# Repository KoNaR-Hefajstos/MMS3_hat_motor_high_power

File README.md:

# Hat Motor High Power

Dostosowany do 48V, ale można zmienić XXX żeby pracować na większym napięciu aż do 100V

Up to 100V 10A

# Dokumentacja
https://github.com/Themuse061/Moducard_System_Handbook

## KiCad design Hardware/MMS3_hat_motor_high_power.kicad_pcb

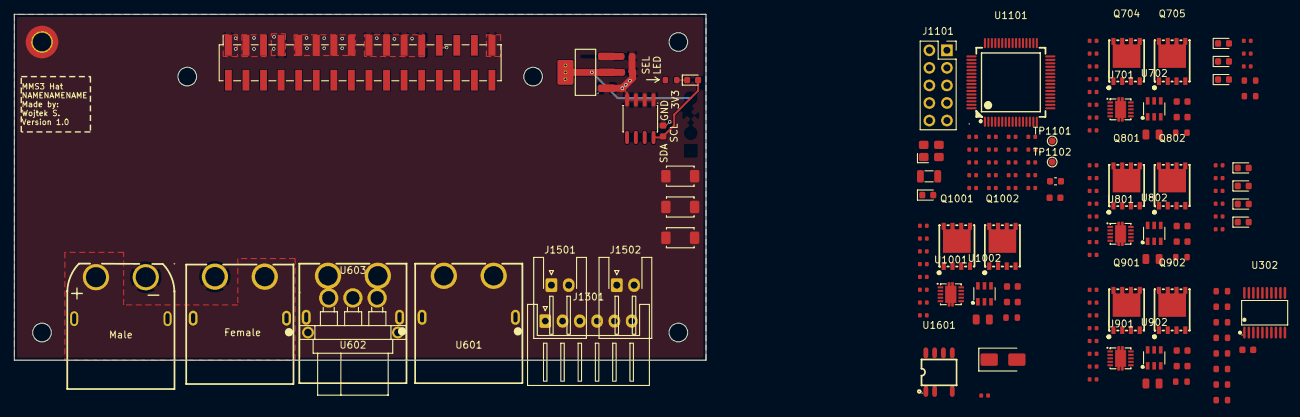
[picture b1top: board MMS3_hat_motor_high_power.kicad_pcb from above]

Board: 2 copper layers, 100.0 x 50.0 mm, 150 parts (1 on the bottom side), 117 nets.

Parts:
C101, C102, C1101: 10uF; C_0603
C301, C501, C703, C704, C802, C804, C902, C904, C1002, C1004: 100nF; C_0603
C701, C708, C803, C808, C903, C908, C1003, C1008, C1102, C1105, C1107, C1109, C1110, C1113, C1114: 100nF; C_0402
C702, C801, C901, C1001: 4.7uF; C_0805
C1103, C1111: 22pF; C_0402
C1104, C1108: 12pF; C_0402
C1106, C1112: 10uF; C_0402
CN401: XT60PW-M; C98732_CONN-TH_XT60PW-M
D301, D601, D603, D607, D1501, D1502, D1503, D1504: Red; D_0603
D401: M7; D_SMA
D701, D801, D901, D1001: D_TVS; R_0402
D1101: Yellow; D_0603
FB1101: FB_0603
H101: M2.5 Mount; MountingHole_2.7mm_M2.5_DIN965_Pad_TopOnly
H102, H103, H104, H105, H106: M2.5 mount; MountingHole_2.7mm_M2.5
J201: Chainbus in; PinHeader_2x16_P2.54mm_Vertical_SMD
J202: Chainbus Out; PinSocket_2x16_P2.54mm_Vertical_SMD
J1101: WCH Link; PinSocket_2x05_P2.54mm_Vertical
J1301: Conn_01x06; JST_XH_S6B-XH-A_1x06_P2.50mm_Horizontal
J1501, J1502: Conn_01x02; JST_XH_S2B-XH-A-1_1x02_P2.50mm_Horizontal
Q704, Q705, Q801, Q802, Q901, Q902, Q1001, Q1002: XRS80N12F; C42457090_DFN-8_L5_8-W4_9-P1_27-LS6_1-BL
R301, R302, R303, R304, R307, R308, R309, R312: 10kΩ; R_0603
R311: 1kΩ; R_0603
R601, R604, R703, R802, R902, R1002: 220kΩ; R_0603
R602, R704, R804, R904, R1004: 6.8kΩ; R_0402
R603, R1107, R1501, R1502, R1503, R1504: 1kΩ; R_0402
R605: 12kΩ; R_0402
R701, R702, R801, R803, R901, R903, R1001, R1003, R1101: 0Ω; R_0402
R706, R707, R806, R807, R906, R907, R1006, R1007, R1102, R1103, R1104, R1105, R1106, R1401, R1505, R1506: 10kΩ; R_0402
S1101, S1102, S1103: Tactile Button, 160gf; SW_TS-1088-AR02016
TP1101, TP1102: TestPoint; TestPoint_Pad_D1.0mm
U101: AMS1117; SOT-223-3_L6.5-W3.4-P2.30-LS7.0-BR
U302: SN74CB3Q3245PWR; C470961_TSSOP-20_L6_5-W4_4-P0_65-LS6_4-BL
U401, U601, U602: XT60PW-F_C428722; C428722_TH_2P-XT60PW-F
U501: M24C64; SOIC-8_L5.0-W4.0-P1.27-LS6.0-BL
U603: MR30PW-F20.G.Y; C19268035_CONN-TH_MR30PW-F
U701, U801, U901, U1001: UCC27302ADRCR; C50092311_VSON-10_L3_0-W3_0-P0_50-TL-EP
U702, U802, U902, U1002: INA181A2IDBVR(LX); C53198613_SOT-23-6_L2_9-W1_6-P0_95-LS2_8-BL
U1101: CH32V305RBT6; C5187529_LQFP-64_L10_0-W10_0-P0_50-LS12_0-BL
U1601: LNK3204D-TL; C567600_SO-8C_7P-L4_9-W3_9-P1_27-LS6_0-BL-PE3
X1101: X322525MOB4SI; OSC-SMD_4P-L3.2-W2.5-BL
X1102: Q13FC1350000400; FC-135R_L3.2-W1.5

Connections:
+3V3: C102.1, C301.1, C501.1, C708.1, C808.1, C908.1, C1008.1, C1101.1, C1102.1, C1105.1, C1106.1, C1107.1, C1110.1, D301.2, FB1101.1, J1101.8, J1301.2, J1501.1, J1502.1, R301.1, R302.1, R304.1, R308.1, R312.1, R603.1, R707.1, R807.1, R907.1, R1007.1, R1101.1, R1104.1, R1105.1, R1401.1, S1101.1 (A), S1102.1 (A), TP1101.1 (1_1), U101.2 (VOUT), U101.4 (VOUT), U302.20 (VCC), U501.8 (VCC), U702.6 (VS), U802.6 (VS), U902.6 (VS), U1002.6 (VS), U1101.19 (VDD_4), U1101.32 (VIO_1), U1101.48 (VDD_2), U1101.64 (VIO_3)
+5V: C101.1, J201.3, J201.5, J202.3, J202.5, J1101.10, U101.3 (VIN)
+12V: C702.1, C703.1, C801.1, C802.1, C901.1, C902.1, C1001.1, C1002.1, R605.1, U701.1 (VDD), U801.1 (VDD), U901.1 (VDD), U1001.1 (VDD)
+12V stby: J201.29, J202.29
/Bus_switch/Chainbus.SCL: R304.2, U302.11 (B8), U501.6 (SCL)
/Bus_switch/Chainbus.SDA: R308.2, U302.12 (B7), U501.5 (SDA)
/Bus_switch/Chainbus_In.CS: J201.22, J202.22, U302.7 (A6)
/Bus_switch/Chainbus_In.MISO: J201.28, J202.28, U302.4 (A3)
/Bus_switch/Chainbus_In.MOSI: J201.26, J202.26, U302.5 (A4)
/Bus_switch/Chainbus_In.SCK: J201.24, J202.24, U302.6 (A5)
/Bus_switch/Chainbus_In.SCL: J201.20, J202.20, U302.9 (A8)
/Bus_switch/Chainbus_In.SDA: J201.18, J202.18, U302.8 (A7)
/Bus_switch/SEL1: J201.2, R311.1, R312.2, U302.19 (OE#)
/Interboard_connector/Chainbus.RX: J201.32, J202.32
/Interboard_connector/Chainbus.TX: J201.30, J202.30
/Interboard_connector/Pin_25: J201.25, J202.25
/Interboard_connector/Pin_27: J201.27, J202.27
/Interboard_connector/SEL2: J201.4, J202.2
/Interboard_connector/SEL3: J201.6, J202.4
/Interboard_connector/SEL4: J201.8, J202.6
/Interboard_connector/SEL5: J201.10, J202.8
/Interboard_connector/SEL6: J201.12, J202.10
/Interboard_connector/SEL7: J201.14, J202.12
/Interboard_connector/SEL8: J201.16, J202.14
/Power Connector/VIN_BRD: CN401.2 (+), D401.2, U401.3 (+)
/User Area/ADC0: C701.1, R703.2, R704.1, U1101.8 (PC0/ADC10)
/User Area/ADC1: U702.1 (OUT), U1101.9 (PC1/ADC11)
/User Area/ADC2: U802.1 (OUT), U1101.10 (PC2/ADC12)
/User Area/ADC3: C803.1, R802.2, R804.1, U1101.11 (PC3/ADC13)
/User Area/ADC4: U902.1 (OUT), U1101.24 (PC4/ADC14)
/User Area/ADC5: C903.1, R902.2, R904.1, U1101.25 (PC5/ADC15)
/User Area/ADC6: U1002.1 (OUT), U1101.15 (PA1/ADC1)
/User Area/ADC7: C1003.1, R1002.2, R1004.1, U1101.16 (PA2/ADC2)
/User Area/CH32V305RBT6/CH32V305RBT6 minimal circuit/BOOT0: R1103.1, S1102.2 (B), U1101.60 (BOOT0)
/User Area/CH32V305RBT6/CH32V305RBT6 minimal circuit/NRST: C1114.1, J1101.9, R1104.2, S1103.1 (A), U1101.7 (NRST)
/User Area/CH32V305RBT6/CH32V305RBT6 minimal circuit/OSC32IN: C1104.1, U1101.3 (PC14/OSC32IN), X1102.1
/User Area/CH32V305RBT6/CH32V305RBT6 minimal circuit/OSC32OUT: C1108.1, U1101.4 (PC15/OSC32OUT), X1102.2
/User Area/CH32V305RBT6/CH32V305RBT6 minimal circuit/OSCIN: C1103.1, U1101.5 (OSC_IN/PD0), X1101.1 (OSC)
/User Area/CH32V305RBT6/CH32V305RBT6 minimal circuit/OSCOUT: C1111.1, U1101.6 (OSC_OUT/PD1), X1101.3 (OSC)
/User Area/CH32V305RBT6/CH32V305RBT6 minimal circuit/PB2/BOOT1: R1105.2, R1106.1, U1101.28 (PB2/BOOT1)
/User Area/CH32V305RBT6/CH32V305RBT6 minimal circuit/PC13/TAMPER-RTC: R1102.1, S1101.2 (B), U1101.2 (PC13/TAMPER-RTC)
/User Area/CH32V305RBT6/CH32V305RBT6 minimal circuit/PD2: R1107.1, U1101.54 (PD2)
/User Area/CH32V305RBT6/CH32V305RBT6 minimal circuit/SWCLK: J1101.2, U1101.49 (PA14/SWCLK)
/User Area/CH32V305RBT6/CH32V305RBT6 minimal circuit/SWDIO: J1101.4, U1101.46 (PA13/SWDIO)
/User Area/CH32V305RBT6/CH32V305RBT6 minimal circuit/UART4_RX: J1101.3, U1101.52 (PC11)
/User Area/CH32V305RBT6/CH32V305RBT6 minimal circuit/UART4_TX: J1101.1, U1101.51 (PC10)
/User Area/CH32V305RBT6/CH32V305RBT6 minimal circuit/VDDA: C1109.1, C1112.1, FB1101.2, TP1102.1 (1_1), U1101.13 (VDDA)
/User Area/CH32V305RBT6/GPIOA3: R1401.2, U1101.17 (PA3/ADC3)
/User Area/CH32V305RBT6/GPIOA15: J1301.6, U1101.50 (PA15)
/User Area/CH32V305RBT6/GPIOB0: R601.2, R602.1, U1101.26 (PB0/ADC8)
/User Area/CH32V305RBT6/GPIOB3: J1301.3, U1101.55 (PB3)
/User Area/CH32V305RBT6/GPIOB4: J1301.5, U1101.56 (PB4)
/User Area/CH32V305RBT6/GPIOB5: J1301.4, U1101.57 (PB5)
/User Area/CH32V305RBT6/GPIOB6: J1501.2, R1505.2, U1101.58 (PB6/USB2DM)
/User Area/CH32V305RBT6/GPIOB7: J1502.2, R1506.2, U1101.59 (PB7/USB2DP)
/User Area/CH32V305RBT6/GPIOB8: R1501.1, U1101.61 (PB8)
/User Area/CH32V305RBT6/GPIOB9: R1502.1, U1101.62 (PB9)
/User Area/CH32V305RBT6/GPIOB10: R1503.1, U1101.29 (PB10)
/User Area/CH32V305RBT6/GPIOB11: R1504.1, U1101.30 (PB11)
/User Area/CH32V305RBT6/GPIOB12: U701.6 (EN), U801.6 (EN), U901.6 (EN), U1001.6 (EN), U1101.33 (PB12)
/User Area/Chainbus.CS: R301.2, U302.13 (B6), U1101.20 (PA4/ADC4/DAC0)
/User Area/Chainbus.MISO: R307.1, U302.16 (B3), U1101.22 (PA6/ADC6)
/User Area/Chainbus.MOSI: R309.1, U302.15 (B4), U1101.23 (PA7/ADC7)
/User Area/Chainbus.SCK: R302.2, R303.1, U302.14 (B5), U1101.21 (PA5/ADC5/DAC1)
/User Area/Half H bridge1/HO: R801.1, U801.4 (HO)
/User Area/Half H bridge1/HS: C804.2, D801.2 (A2), Q801.5 (D), Q801.6 (D), Q801.7 (D), Q801.8 (D), Q801.9 (D), Q802.1 (S), Q802.2 (S), Q802.3 (S), R802.1, U602.4 (-), U603.2, U801.5 (HS)
/User Area/Half H bridge1/LO: R803.1, U801.10 (LO)
/User Area/Half H bridge1/Shunt+: Q801.1 (S), Q801.2 (S), Q801.3 (S), U802.3 (IN+)
/User Area/Half H bridge2/HO: R901.1, U901.4 (HO)
/User Area/Half H bridge2/HS: C904.2, D901.2 (A2), Q901.5 (D), Q901.6 (D), Q901.7 (D), Q901.8 (D), Q901.9 (D), Q902.1 (S), Q902.2 (S), Q902.3 (S), R902.1, U601.3 (+), U603.3, U901.5 (HS)
/User Area/Half H bridge2/LO: R903.1, U901.10 (LO)
/User Area/Half H bridge2/Shunt+: Q901.1 (S), Q901.2 (S), Q901.3 (S), U902.3 (IN+)
/User Area/Half H bridge3/HO: R1001.1, U1001.4 (HO)
/User Area/Half H bridge3/HS: C1004.2, D1001.2 (A2), Q1001.5 (D), Q1001.6 (D), Q1001.7 (D), Q1001.8 (D), Q1001.9 (D), Q1002.1 (S), Q1002.2 (S), Q1002.3 (S), R1002.1, U601.4 (-), U1001.5 (HS)
/User Area/Half H bridge3/LO: R1003.1, U1001.10 (LO)
/User Area/Half H bridge3/Shunt+: Q1001.1 (S), Q1001.2 (S), Q1001.3 (S), U1002.3 (IN+)
/User Area/Half H bridge/HO: R701.1, U701.4 (HO)
/User Area/Half H bridge/HS: C704.2, D701.2 (A2), Q704.1 (S), Q704.2 (S), Q704.3 (S), Q705.5 (D), Q705.6 (D), Q705.7 (D), Q705.8 (D), Q705.9 (D), R703.1, U602.3 (+), U603.1, U701.5 (HS)
/User Area/Half H bridge/LO: R702.1, U701.10 (LO)
/User Area/Half H bridge/Shunt+: Q705.1 (S), Q705.2 (S), Q705.3 (S), U702.3 (IN+)
/User Area/Mosfet0: U701.7 (HI), U1101.41 (PA8)
/User Area/Mosfet1: U701.8 (LI), U1101.34 (PB13)
/User Area/Mosfet2: U801.7 (HI), U1101.42 (PA9)
/User Area/Mosfet3: U801.8 (LI), U1101.35 (PB14)
/User Area/Mosfet4: U901.7 (HI), U1101.43 (PA10)
/User Area/Mosfet5: U901.8 (LI), U1101.36 (PB15)
/User Area/Mosfet6: U1001.7 (HI), U1101.38 (PC7)
/User Area/Mosfet7: U1001.8 (LI), U1101.39 (PC8)
/User Area/VIN: Q704.5 (D), Q704.6 (D), Q704.7 (D), Q704.8 (D), Q704.9 (D), Q802.5 (D), Q802.6 (D), Q802.7 (D), Q802.8 (D), Q802.9 (D), Q902.5 (D), Q902.6 (D), Q902.7 (D), Q902.8 (D), Q902.9 (D), Q1002.5 (D), Q1002.6 (D), Q1002.7 (D), Q1002.8 (D), Q1002.9 (D), R601.1, R604.1
GND: C101.2, C102.2, C301.2, C501.2, C701.2, C702.2, C703.2, C708.2, C801.2, C802.2, C803.2, C808.2, C901.2, C902.2, C903.2, C908.2, C1001.2, C1002.2, C1003.2, C1008.2, C1101.2, C1102.2, C1103.2, C1104.2, C1105.2, C1106.2, C1107.2, C1108.2, C1109.2, C1110.2, C1111.2, C1112.2, C1113.2, C1114.2, CN401.1 (-), D601.1, D603.1, D607.1, D701.1 (A1), D801.1 (A1), D901.1 (A1), D1001.1 (A1), D1101.1, D1501.1, D1502.1, D1503.1, D1504.1, H101.1 (1_1), J201.1, J201.7, J201.17, J201.19, J201.21, J201.23, J201.31, J202.1, J202.7, J202.17, J202.19, J202.21, J202.23, J202.31, J1101.6, J1301.1, R303.2, R307.2, R309.2, R602.2, R704.2, R706.2, R804.2, R806.2, R904.2, R906.2, R1004.2, R1006.2, R1102.2, R1103.2, R1106.2, R1505.1, R1506.1, S1103.2 (B), U101.1 (GND), U302.10 (GND), U401.4 (-), U501.1 (A0), U501.2 (A1), U501.3 (A2), U501.4 (VSS), U701.9 (VSS), U701.11 (EP), U702.2 (GND), U702.4 (IN-), U801.9 (VSS), U801.11 (EP), U802.2 (GND), U802.4 (IN-), U901.9 (VSS), U901.11 (EP), U902.2 (GND), U902.4 (IN-), U1001.9 (VSS), U1001.11 (EP), U1002.2 (GND), U1002.4 (IN-), U1101.12 (VSSA), U1101.18 (VSS_4), U1101.31 (VSS_1), U1101.47 (VSS_2), U1101.63 (VSS_3), X1101.2 (GND), X1101.4 (GND)
unnamed: D301.1, R311.2
unnamed: D601.2, R605.2
unnamed: D603.2, R603.2
unnamed: D607.2, R604.2
unnamed: D1101.2, R1107.2
unnamed: D1501.2, R1501.2
unnamed: D1502.2, R1502.2
unnamed: D1503.2, R1503.2
unnamed: D1504.2, R1504.2
unnamed: Q704.4 (G), R701.2
unnamed: Q705.4 (G), R702.2
unnamed: Q801.4 (G), R803.2
unnamed: Q802.4 (G), R801.2
unnamed: Q901.4 (G), R903.2
unnamed: Q902.4 (G), R901.2
unnamed: Q1001.4 (G), R1003.2
unnamed: Q1002.4 (G), R1001.2
unnamed: C704.1, U701.3 (HB)
unnamed: R706.1, R707.2, U702.5 (REF)
unnamed: C804.1, U801.3 (HB)
unnamed: R806.1, R807.2, U802.5 (REF)
unnamed: C904.1, U901.3 (HB)
unnamed: R906.1, R907.2, U902.5 (REF)
unnamed: C1004.1, U1001.3 (HB)
unnamed: R1006.1, R1007.2, U1002.5 (REF)
unnamed: C1113.1, R1101.2, U1101.1 (VBAT)
VIN_CHAINBUS: D401.1, J201.9, J201.11, J201.13, J201.15, J202.9, J202.11, J202.13, J202.15
